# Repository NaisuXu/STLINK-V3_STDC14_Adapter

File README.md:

# STLINK-V3_STDC14_Adapter

## Brief

An adapter board for STLINK-V3. It change the STDC14 to 2.54mm pin header.It also provides 5V and 3.3V power supply through an additional USB interface.

This project is designed with [Kicad](https://www.kicad.org/).

## Images

## License
<br />This work is licensed under a <a rel="license" href="http://creativecommons.org/licenses/by-sa/4.0/">Creative Commons Attribution-ShareAlike 4.0 International License</a>.

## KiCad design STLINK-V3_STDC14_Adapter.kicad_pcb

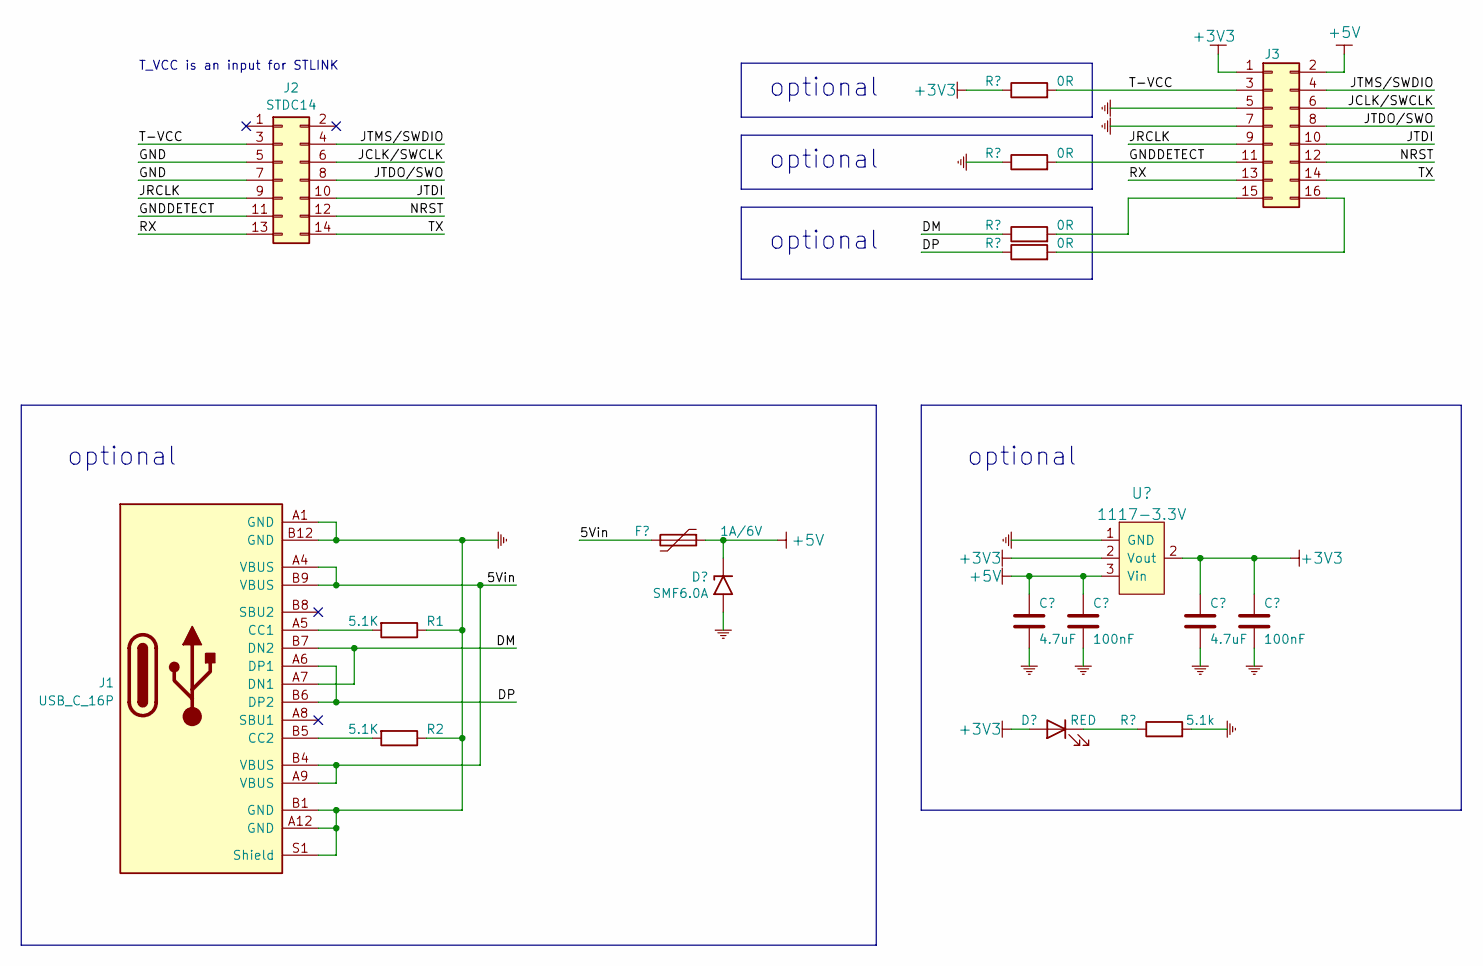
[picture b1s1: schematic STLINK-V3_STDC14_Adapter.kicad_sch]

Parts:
C1, C3: 4.7uF; C_0805_2012Metric_Pad1.18x1.45mm_HandSolder
C2, C4: 100nF; C_0603_1608Metric_Pad1.08x0.95mm_HandSolder
D2: SMF6.0A; D_1206_3216Metric_Pad1.42x1.75mm_HandSolder
D3: RED; LED_0603_1608Metric_Pad1.05x0.95mm_HandSolder
F1: 1A/6V; Fuse_1206_3216Metric_Pad1.42x1.75mm_HandSolder
J1: USB_C_16P; USB_C_16P_4Foot8.64mm
J2: STDC14; DC3_SMD_14P_1.27mm
J3: DC3; PinHeader_2x08_P2.54mm_Horizontal
R1, R2: 5.1K; R_0603_1608Metric
R4, R5, R6, R7: 0R; R_0603_1608Metric_Pad0.98x0.95mm_HandSolder
R8: 5.1k; R_0603_1608Metric_Pad0.98x0.95mm_HandSolder
U1: 1117-3.3V; SOT-223-3_TabPin2

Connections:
+3V3: C3.1, C4.1, D3.2 (A), J3.1, R6.1, U1.2 (Vout)
+5V: C1.1, C2.1, D2.1 (A1), F1.1, J3.2, U1.3 (Vin)
/5Vin: F1.2, J1.A4 (VBUS), J1.A9 (VBUS), J1.B4 (VBUS), J1.B9 (VBUS)
/DM: J1.A7 (DN1), J1.B7 (DN2), R4.1
/DP: J1.A6 (DP1), J1.B6 (DP2), R5.1
/GNDDETECT: J2.11, J3.11, R7.2
/JCLK/SWCLK: J2.6, J3.6
/JRCLK: J2.9, J3.9
/JTDI: J2.10, J3.10
/JTDO/SWO: J2.8, J3.8
/JTMS/SWDIO: J2.4, J3.4
/NRST: J2.12, J3.12
/RX: J2.13, J3.13
/T-VCC: J2.3, J3.3, R6.2
/TX: J2.14, J3.14
GND: C1.2, C2.2, C3.2, C4.2, D2.2 (A2), J1.A1 (GND), J1.A12 (GND), J1.B1 (GND), J1.B12 (GND), J1.S1 (Shield), J2.5, J2.7, J3.5, J3.7, R1.1, R2.1, R7.1, R8.2, U1.1 (GND)
unnamed: D3.1 (K), R8.1
unnamed: J1.A5 (CC1), R1.2
unnamed: J1.B5 (CC2), R2.2
unnamed: J3.15, R4.2
unnamed: J3.16, R5.2

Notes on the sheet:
optional
T_VCC is an input for STLINK

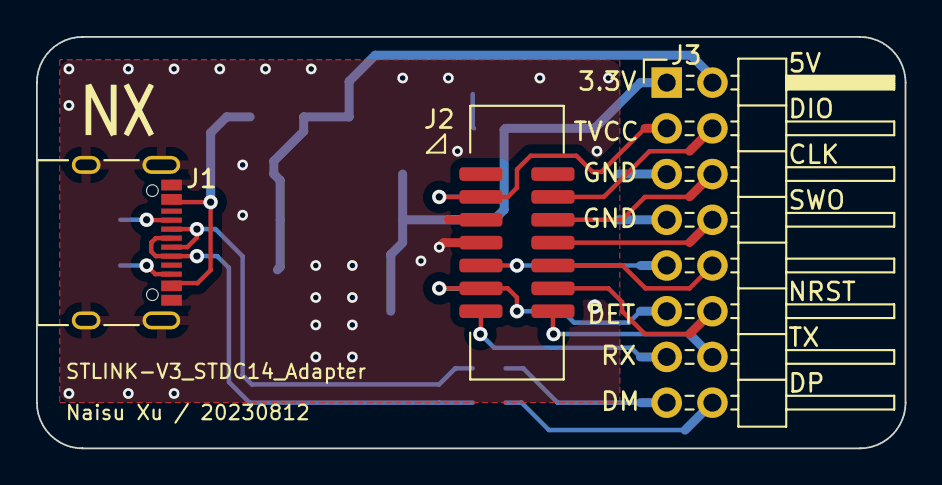
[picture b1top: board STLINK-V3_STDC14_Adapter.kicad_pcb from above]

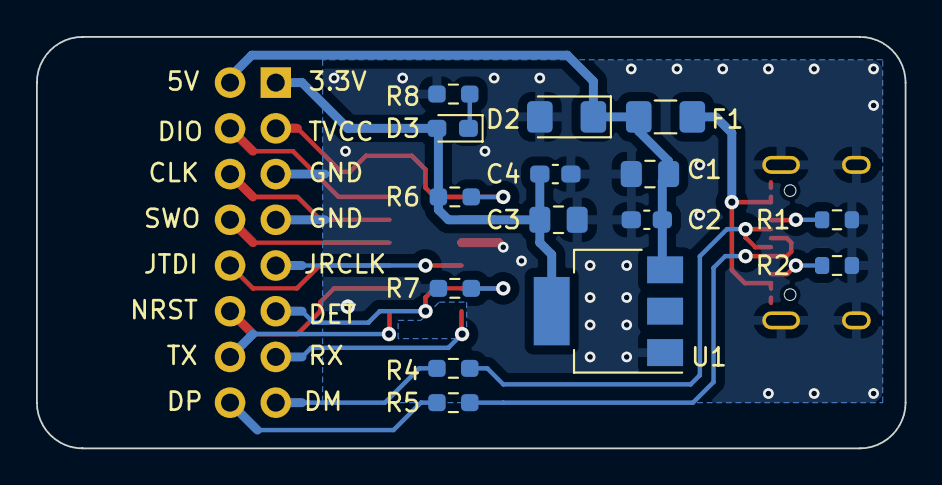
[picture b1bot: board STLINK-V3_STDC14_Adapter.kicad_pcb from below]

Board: 2 copper layers, 48.3 x 22.9 mm, 18 parts (15 on the bottom side), 21 nets.

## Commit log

2023-09-12 feat: first commit.
2023-09-12 update: README.md
